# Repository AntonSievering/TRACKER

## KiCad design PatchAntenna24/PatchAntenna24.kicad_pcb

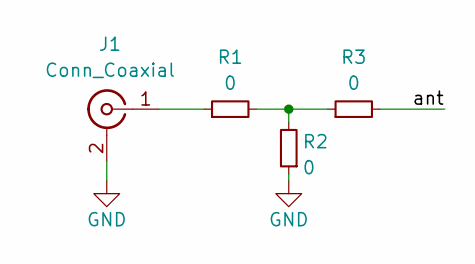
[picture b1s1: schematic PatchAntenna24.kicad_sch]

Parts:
J1: Conn_Coaxial; SMA_Amphenol_132289_EdgeMount
R1, R2, R3: 0; R_0402_1005Metric

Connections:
/ant: R3.2
GND: J1.2 (Ext), R2.1
unnamed: J1.1 (In), R1.1
unnamed: R1.2, R2.2, R3.1

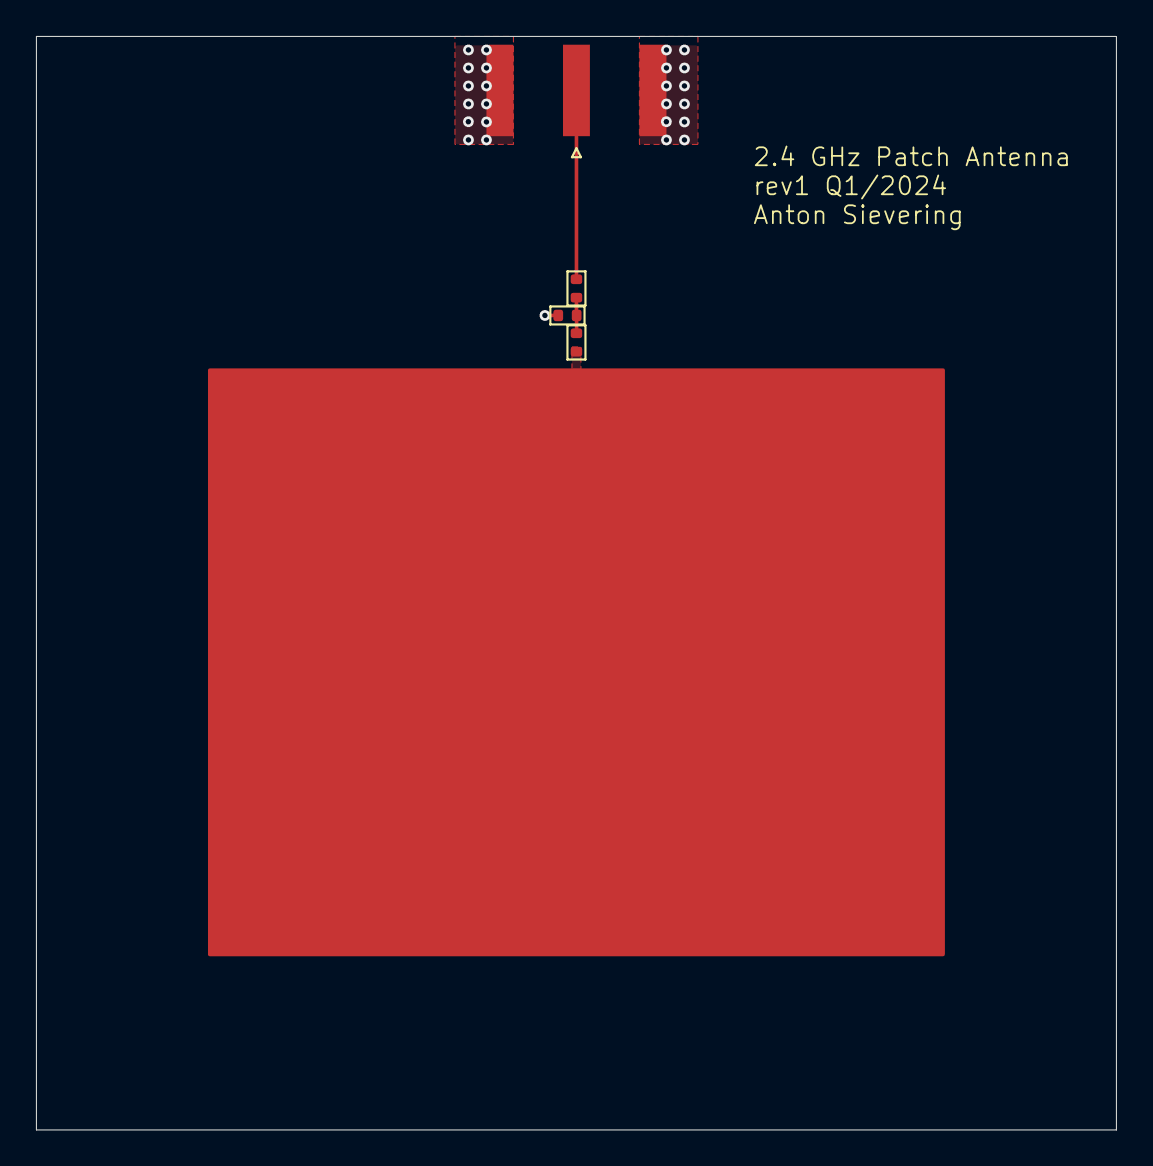
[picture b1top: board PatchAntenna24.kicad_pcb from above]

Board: 4 copper layers, 60.0 x 60.8 mm, 4 parts (0 on the bottom side), 3 nets.

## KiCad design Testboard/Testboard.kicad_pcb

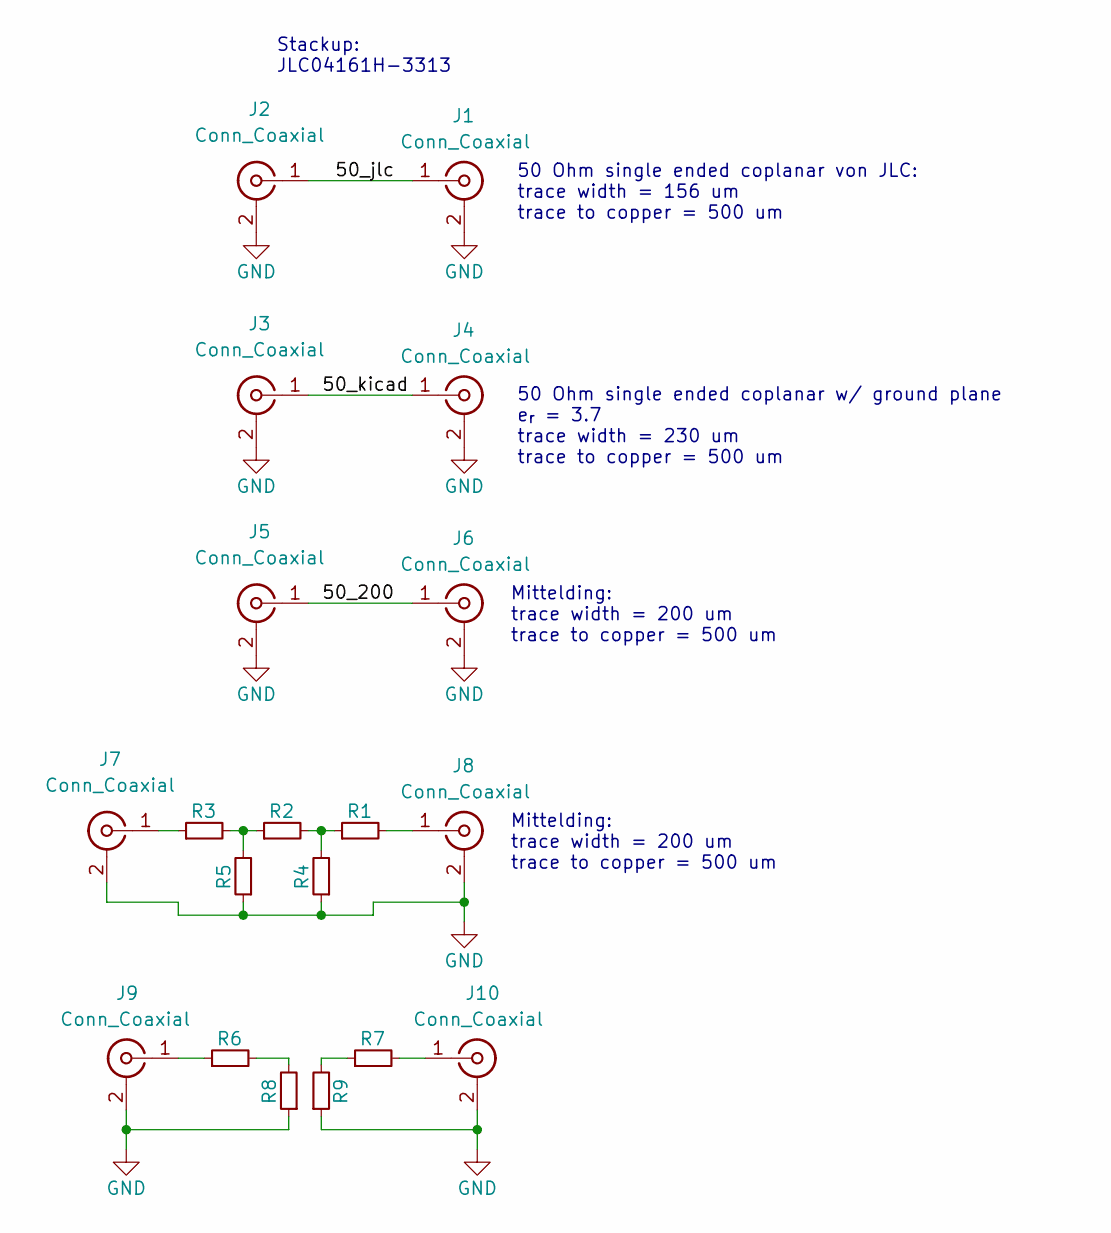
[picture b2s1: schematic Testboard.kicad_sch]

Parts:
J1, J2, J3, J4, J5, J6, J7, J8, J9, J10: Conn_Coaxial; SMA_Amphenol_132289_EdgeMount
R1, R2, R3, R4, R5, R6, R7, R8, R9: R_Small; R_0603_1608Metric

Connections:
/50_200: J5.1 (In), J6.1 (In)
/50_jlc: J1.1 (In), J2.1 (In)
/50_kicad: J3.1 (In), J4.1 (In)
GND: J1.2 (Ext), J2.2 (Ext), J3.2 (Ext), J4.2 (Ext), J5.2 (Ext), J6.2 (Ext), J7.2 (Ext), J8.2 (Ext), J9.2 (Ext), J10.2 (Ext), R4.1, R5.1, R8.1, R9.1
unnamed: J7.1 (In), R3.1
unnamed: J8.1 (In), R1.2
unnamed: J9.1 (In), R6.1
unnamed: J10.1 (In), R7.2
unnamed: R1.1, R2.2, R4.2
unnamed: R2.1, R3.2, R5.2
unnamed: R6.2, R8.2
unnamed: R7.1, R9.2

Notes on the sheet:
50 Ohm single ended coplanar von JLC: trace width = 156 um trace to copper = 500 um
Stackup: JLC04161H-3313
50 Ohm single ended coplanar w/ ground plane e_{r} = 3.7 trace width = 230 um trace to copper = 500 um
Mittelding: trace width = 200 um trace to copper = 500 um

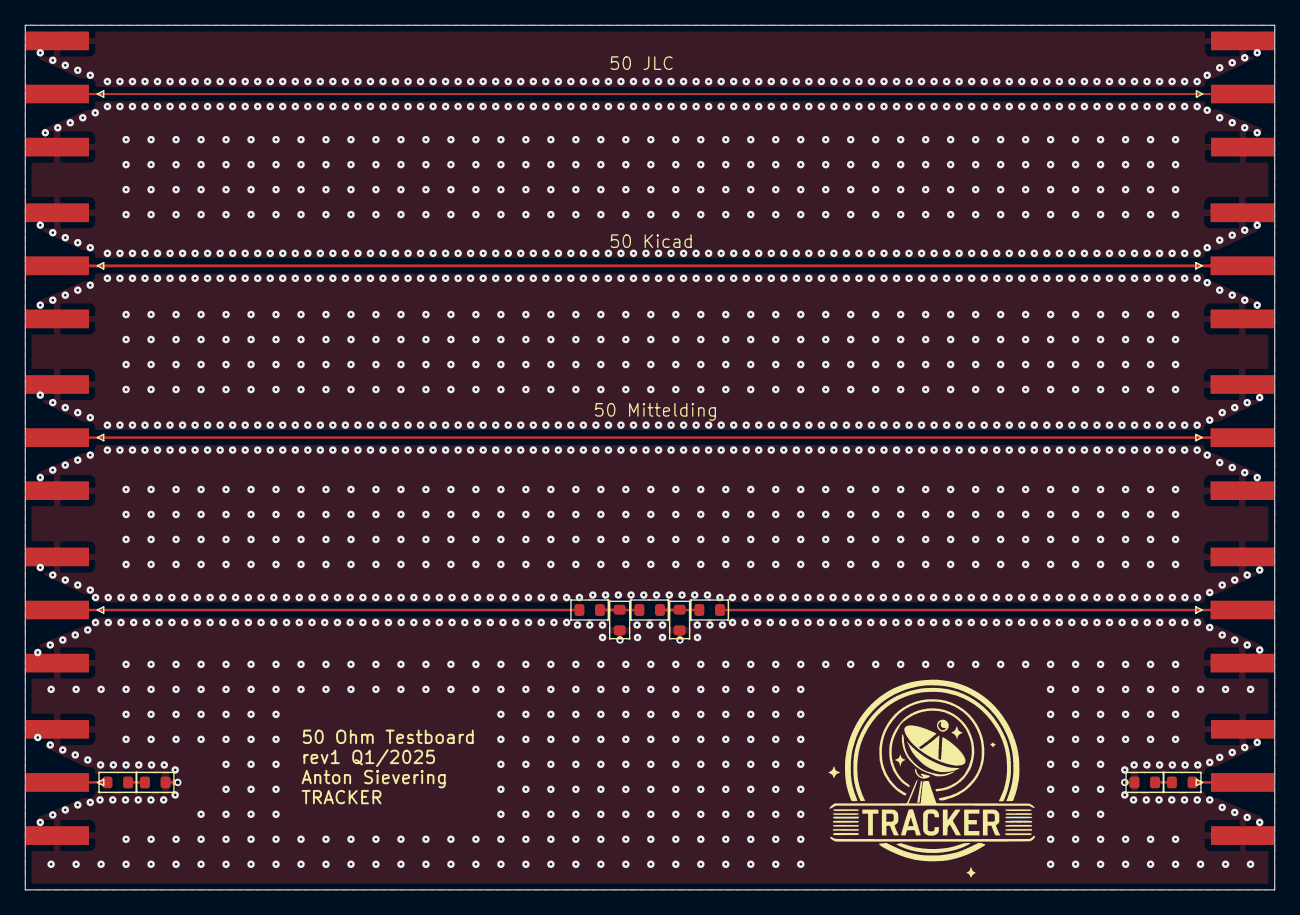
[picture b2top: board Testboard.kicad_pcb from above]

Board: 4 copper layers, 100.0 x 69.2 mm, 19 parts (0 on the bottom side), 12 nets.

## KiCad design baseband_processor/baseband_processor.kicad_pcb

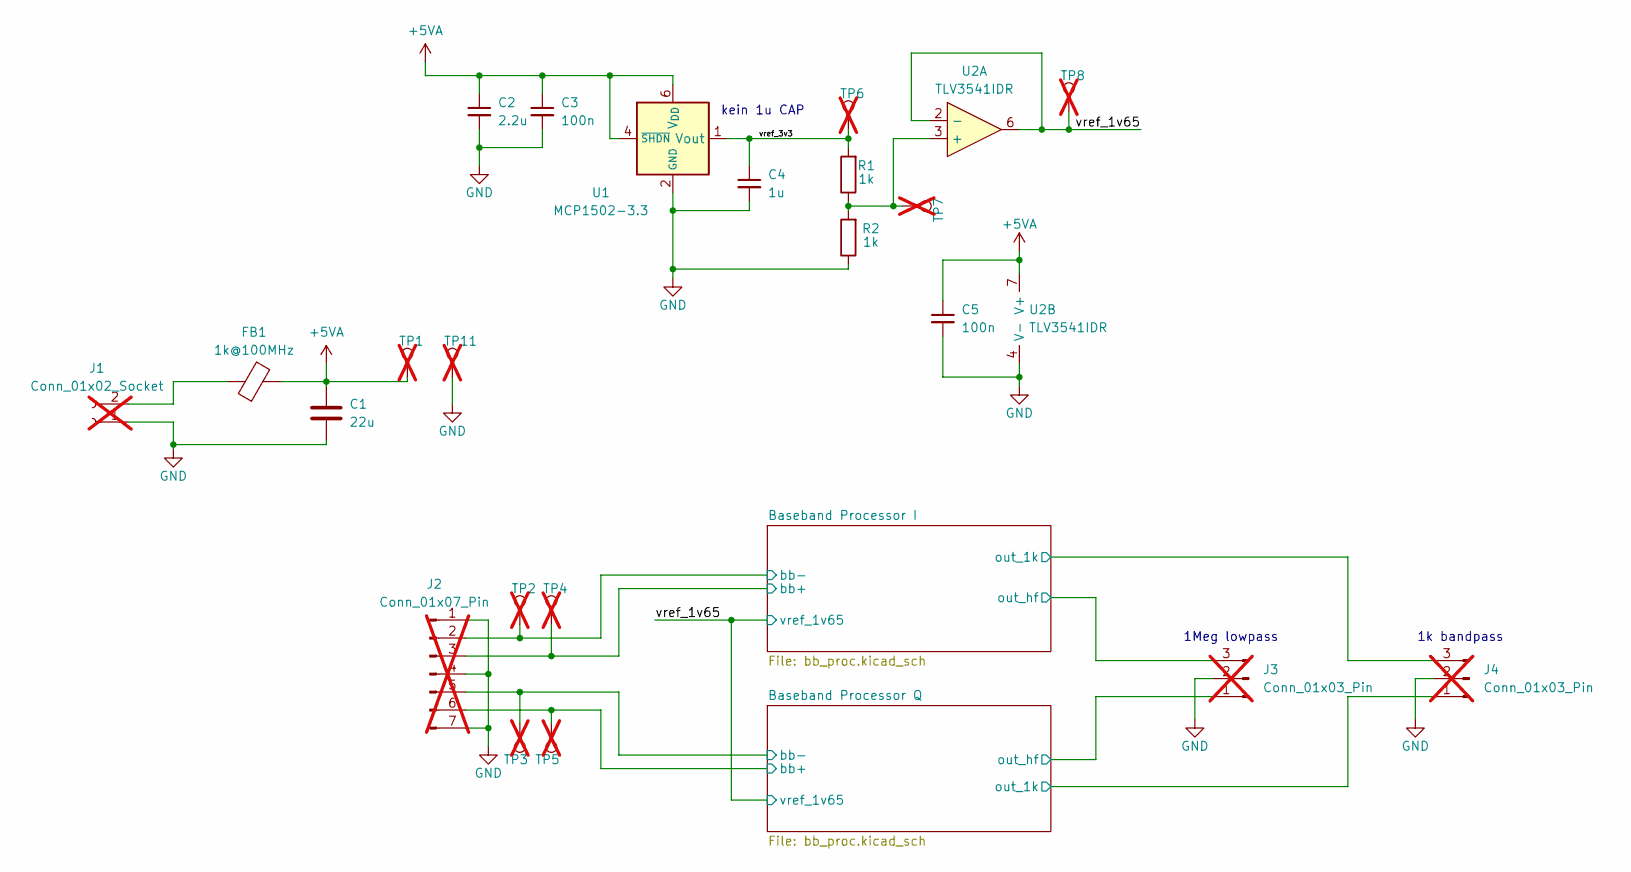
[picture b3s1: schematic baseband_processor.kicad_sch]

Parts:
C1: 22u; R_0805_2012Metric
C2: 2.2u; C_0603_1608Metric
C3, C5: 100n; C_0603_1608Metric
C4: 1u; C_0603_1608Metric
FB1: 1k@100MHz; L_0603_1608Metric; MPN 81-BLM18KG102SH1D
J1: Conn_01x02_Socket; PinHeader_1x02_P2.54mm_Vertical; not fitted
J2: Conn_01x07_Pin; PinHeader_1x07_P2.54mm_Vertical; not fitted
J3, J4: Conn_01x03_Pin; PinHeader_1x03_P2.54mm_Vertical; not fitted
R1, R2: 1k; R_0603_1608Metric
TP1, TP2, TP3, TP4, TP5, TP6, TP7, TP8, TP11: TestPoint; TestPoint_Pad_D1.0mm; not fitted
U1: MCP1502-3.3; TSOT-23-6; MPN 579-MCP1502T-33E/CHY
U2: TLV3541IDR; SOIC-8_3.9x4.9mm_P1.27mm; MPN TLV3541IDR

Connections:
+5VA: C1.1, C2.1, C3.1, C5.1, FB1.2, TP1.1, U1.4 (~SHDN), U1.6 (V_{DD}), U2.7 (V+); also elsewhere on the board
/Baseband Processor I/bb+: J2.3, TP4.1; also elsewhere on the board
/Baseband Processor I/bb-: J2.2, TP2.1; also elsewhere on the board
/Baseband Processor I/out_1k: J4.3; also elsewhere on the board
/Baseband Processor I/out_hf: J3.3; also elsewhere on the board
/Baseband Processor Q/bb+: J2.6, TP5.1; also elsewhere on the board
/Baseband Processor Q/bb-: J2.5, TP3.1; also elsewhere on the board
/Baseband Processor Q/out_1k: J4.1; also elsewhere on the board
/Baseband Processor Q/out_hf: J3.1; also elsewhere on the board
/vref_1v65: TP8.1, U2.2 (-), U2.6; also elsewhere on the board
/vref_3v3: C4.1, R1.2, TP6.1, U1.1 (Vout)
GND: C1.2, C2.2, C3.2, C4.2, C5.2, J1.1, J2.1, J2.4, J2.7, J3.2, J4.2, R2.1, TP11.1, U1.2 (GND), U1.3 (GND), U1.5 (GND), U2.4 (V-); also elsewhere on the board
unnamed: FB1.1, J1.2
unnamed: R1.1, R2.2, TP7.1, U2.3 (+)

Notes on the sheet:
1k bandpass
1Meg lowpass
kein 1u CAP

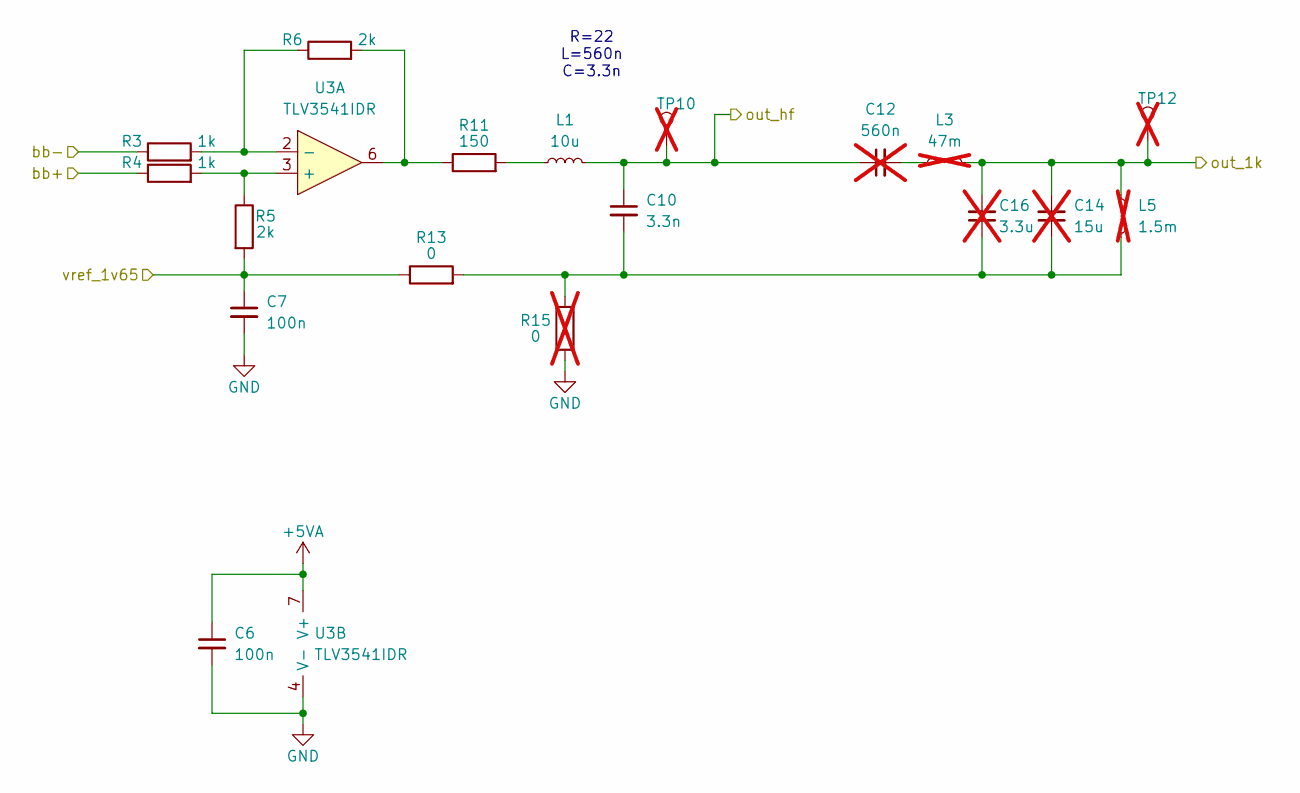
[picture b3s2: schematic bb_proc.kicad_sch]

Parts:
C6, C7: 100n; C_0603_1608Metric
C10: 3.3n; R_0603_1608Metric; MPN GCD188R71H332KA1D
C12: 560n; C_0603_1608Metric; MPN CC603KRX7R7BB564; not fitted
C14: 15u; C_0805_2012Metric; MPN C2012X6S1C156M2A; not fitted
C16: 3.3u; C_0805_2012Metric; MPN 0805X335K250CT; not fitted
L1: 10u; R_0603_1608Metric; MPN MLZ2012M100HT000
L3: 47m; L_Radial_D7.0mm_P3.00mm; MPN RLB0812-473KL; not fitted
L5: 1.5m; L_Radial_D7.0mm_P3.00mm; MPN RLB0608-152KL; not fitted
R3, R4: 1k; R_0603_1608Metric
R5, R6: 2k; R_0603_1608Metric
R11: 150; R_0603_1608Metric
R13: 0; R_0603_1608Metric
R15: 0; R_0603_1608Metric; not fitted
TP10, TP12: TestPoint; TestPoint_Pad_D1.0mm; not fitted
U3: TLV3541IDR; SOIC-8_3.9x4.9mm_P1.27mm; MPN TLV3541IDR

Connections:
+5VA: C6.1, U3.7 (V+); also elsewhere on the board
/Baseband Processor I/bb+: R4.1; also elsewhere on the board
/Baseband Processor I/bb-: R3.1; also elsewhere on the board
/Baseband Processor I/out_1k: C14.2, C16.2, L3.2, L5.1, TP12.1; also elsewhere on the board
/Baseband Processor I/out_hf: C10.1, C12.1, L1.2, TP10.1; also elsewhere on the board
/vref_1v65: C7.1, R5.2, R13.1; also elsewhere on the board
GND: C6.2, C7.2, R15.1, U3.4 (V-); also elsewhere on the board
unnamed: C10.2, C14.1, C16.1, L5.2, R13.2, R15.2
unnamed: C12.2, L3.1
unnamed: L1.1, R11.2
unnamed: R6.2, R11.1, U3.6
unnamed: R4.2, R5.1, U3.3 (+)
unnamed: R3.2, R6.1, U3.2 (-)

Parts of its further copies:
C8, C9: 100n; C_0603_1608Metric
C11: 3.3n; R_0603_1608Metric; MPN GCD188R71H332KA1D
C13: 560n; C_0603_1608Metric; MPN CC603KRX7R7BB564; not fitted
C15: 15u; C_0805_2012Metric; MPN C2012X6S1C156M2A; not fitted
C17: 3.3u; C_0805_2012Metric; MPN 0805X335K250CT; not fitted
L2: 10u; R_0603_1608Metric; MPN MLZ2012M100HT000
L4: 47m; L_Radial_D7.0mm_P3.00mm; MPN RLB0812-473KL; not fitted
L6: 1.5m; L_Radial_D7.0mm_P3.00mm; MPN RLB0608-152KL; not fitted
R7, R8: 1k; R_0603_1608Metric
R9, R10: 2k; R_0603_1608Metric
R12: 150; R_0603_1608Metric
R14: 0; R_0603_1608Metric
R16: 0; R_0603_1608Metric; not fitted
TP9, TP13: TestPoint; TestPoint_Pad_D1.0mm; not fitted
U4: TLV3541IDR; SOIC-8_3.9x4.9mm_P1.27mm; MPN TLV3541IDR

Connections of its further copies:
+5VA: C8.1, U4.7 (V+); also elsewhere on the board
/Baseband Processor Q/bb+: R8.1; also elsewhere on the board
/Baseband Processor Q/bb-: R7.1; also elsewhere on the board
/Baseband Processor Q/out_1k: C15.2, C17.2, L4.2, L6.1, TP13.1; also elsewhere on the board
/Baseband Processor Q/out_hf: C11.1, C13.1, L2.2, TP9.1; also elsewhere on the board
/vref_1v65: C9.1, R9.2, R14.1; also elsewhere on the board
GND: C8.2, C9.2, R16.1, U4.4 (V-); also elsewhere on the board
unnamed: C11.2, C15.1, C17.1, L6.2, R14.2, R16.2
unnamed: C13.2, L4.1
unnamed: L2.1, R12.2
unnamed: R10.2, R12.1, U4.6
unnamed: R8.2, R9.1, U4.3 (+)
unnamed: R7.2, R10.1, U4.2 (-)

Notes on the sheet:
R=22 L=560n C=3.3n

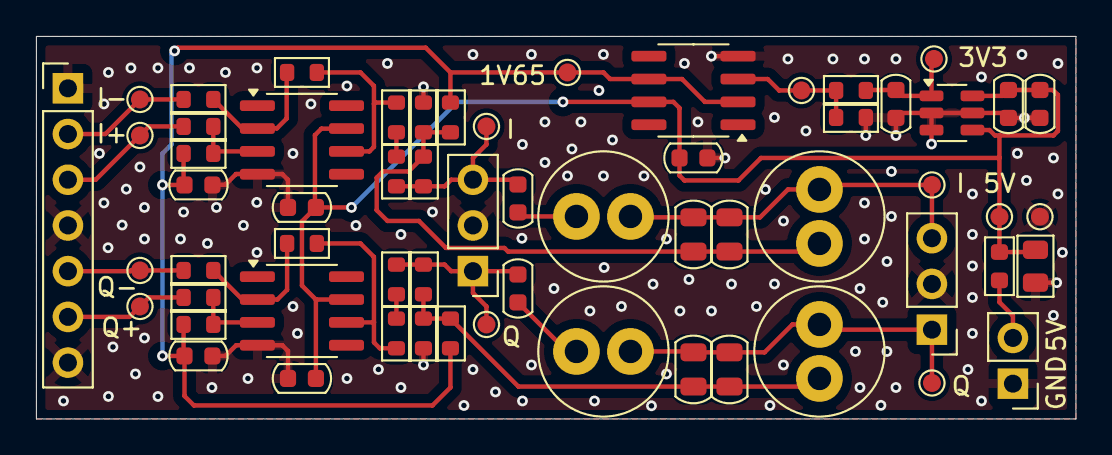
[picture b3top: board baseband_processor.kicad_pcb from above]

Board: 2 copper layers, 57.8 x 21.2 mm, 61 parts (0 on the bottom side), 26 nets.

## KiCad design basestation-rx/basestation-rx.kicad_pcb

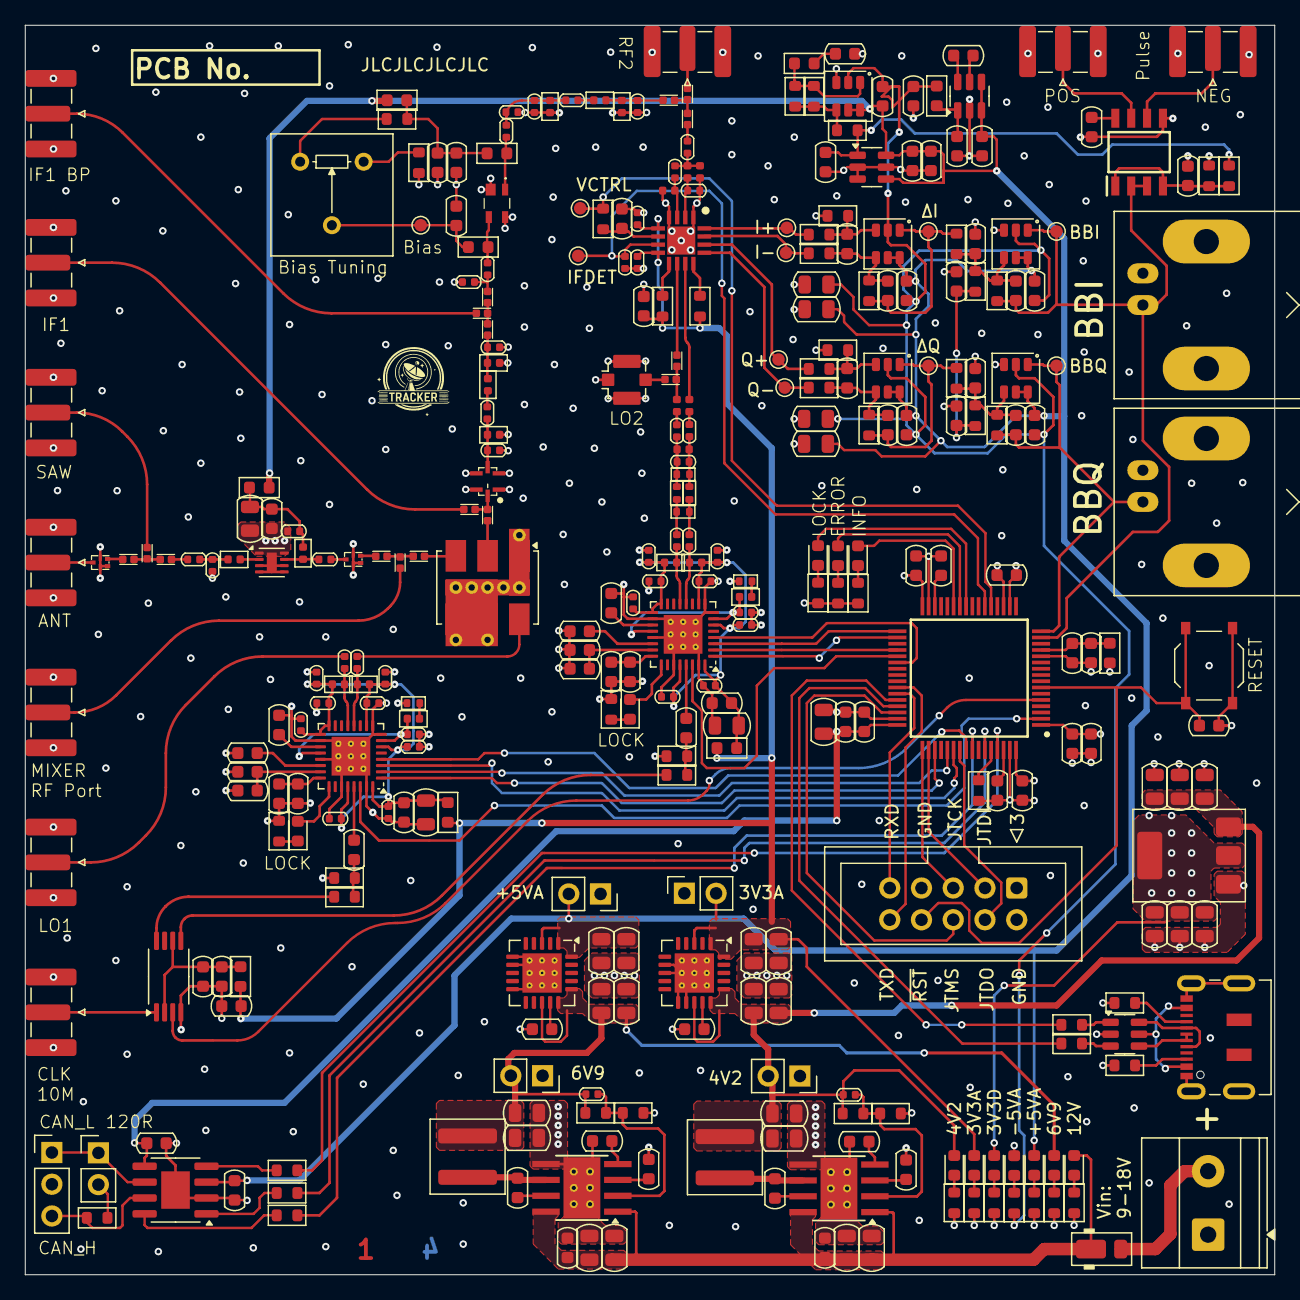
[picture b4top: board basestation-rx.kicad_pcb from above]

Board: 4 copper layers, 100.0 x 100.0 mm, 332 parts (0 on the bottom side), 185 nets.

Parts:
C1, C6, C7, C8, C9, C10, C11, C14, C15, C17, C21, C36, C40, C62, C70, C75, C84, C85, C93, C94, C102, C104, C106, C113, C114, C122, C123, C146, C147: 100n; C_0603_1608Metric
C1_LF1, C1_LF2, C33, C34, C52, C53, C79, C80: 1n; C_0402_1005Metric
C2, C3, C25, C44, C103, C107, C112, C120, C121: 2.2u; C_0603_1608Metric
C2_LF1, C2_LF2: 6.8n; L_0402_1005Metric
C4, C16, C35, C60, C87, C88, C96, C97, C100, C108, C109, C110, C111, C130, C131, C132, C133, C134, C135: 10u; C_0805_2012Metric
C5, C12, C13, C78, C86, C95, C101, C105, C115, C116, C117, C137, C138, C145: 1u; C_0603_1608Metric
C18, C19, C20, C22, C23, C24, C31, C32, C37, C38, C39, C41, C42, C43, C50, C51, C64, C69, C72, C124, C125: 100p; C_0402_1005Metric
C26, C29, C45, C48: 22u; C_0603_1608Metric
C27, C28, C30, C46, C47, C49: 10u; C_0603_1608Metric
C54: 91p; C_0402_1005Metric
C55, C56, C81: 1.5p; C_0402_1005Metric
C57, C66: 27p; C_0402_1005Metric
C58, C67: 3.3p; C_0402_1005Metric
C59, C68: 180p; C_0402_1005Metric
C61: 12p; C_0402_1005Metric
C63: Tuning; C_0402_1005Metric
C65: 2.7p; C_0402_1005Metric
C71, C73, C82, C83, C89, C90, C91, C92, C98, C99: 1n; C_0603_1608Metric
C74: 56p; C_0402_1005Metric
C76, C77: 5.6p; C_0402_1005Metric
C118, C119: 3.3n; C_0603_1608Metric
C126, C127, C128, C129: 22u; C_0805_2012Metric
C136, C139, C140, C141, C142, C143, C144: 47u; C_0805_2012Metric
C148, C149: 15p; C_0402_1005Metric
D1, D2, D3, D4, D5, D6, D7, D8, D9, D11, D12, D13: LED; D_0603_1608Metric
D10: DFLS130; D_PowerDI-123
FB1, FB2, FB3, FB4, FB5, FB6, FB7, FB8: 1k@100MHz; L_0603_1608Metric
IC1: STM32H562RGT6; QFP50P1200X1200X160-64N
IC2, IC3: LMX2581SQE_NOPB; QFN-32-1EP_5x5mm_P0.5mm_EP3.1x3.1mm_ThermalVias
IC4: SAV-551+; SAV551
IC5: LT5546EUF#PBF; QFN65P400X400X80-17N-D
IC6: LMK1C1104PWR; TSSOP-8_4.4x3mm_P0.65mm
J1, J2, J3, J4, J5, J6, J8, J9, J20, J21: SMA; SMA_Edge_Mount
J7: U.FL; U.FL_Molex_MCRF_73412-0110_Vertical
J10: USB_C_Receptacle_USB2.0_16P; USB_C_Receptacle_JAE_DX07S016JA1R1500
J11: Conn_01x02_Pin; PinHeader_1x02_P2.54mm_Vertical
J12: Conn_01x03_Pin; PinHeader_1x03_P2.54mm_Vertical
J13, J15, J16, J17: Conn_01x02_Pin; PinSocket_1x02_P2.54mm_Vertical
J14: Conn_02x05_Counter_Clockwise; IDC-Header_2x05_P2.54mm_Vertical
J18: Screw_Terminal_01x02; TerminalBlock_Phoenix_MKDS-1,5-2-5.08_1x02_P5.08mm_Horizont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
J19, J22: BNC; BNC_Amphenol_B6252HB-NPP3G-50_Horizontal
L1, L2, L3, L4: 18n; L_0402_1005Metric
L5: 1.8n; L_0402_1005Metric
L6, L7: 110n; L_0402_1005Metric
L8, L13: 24n; L_0402_1005Metric
L9, L14: 200n; L_0402_1005Metric
L10, L12, L15: 3.6n; L_0402_1005Metric
L11: 1.5n; L_0402_1005Metric
L16, L17: 560n; L_0603_1608Metric
L18: 120n; L_0402_1005Metric
L19, L20: 56n; L_0402_1005Metric
L23, L24: 3.3u; L_Coilcraft_XAL5030
R1, R4, R41: 1k; R_0603_1608Metric
R2, R3, R6, R7, R8, R9, R10, R11, R13, R14, R15, R16, R17, R18, R19, R20: 0; RF_JUMPER
R2_LF1, R2_LF2: 820R; R_0402_1005Metric
R5, R21, R22, R23, R24, R28, R42, R43: 0; R_0603_1608Metric
R25: 120; R_0603_1608Metric
R26, R27: 5.6k; R_0603_1608Metric
R29, R32, R35, R59, R60, R61, R62, R63, R64, R65, R66, R67, R68, R74, R75: 10k; R_0603_1608Metric
R30, R31, R33, R34: 25R; R_0603_1608Metric
R36, R39: 330R; R_0402_1005Metric
R37, R38: 33R; R_0402_1005Metric
R40, R46, R47, R53, R54: 2k 0.1%; R_0603_1608Metric
R44, R45, R48, R49, R50, R51, R52, R55, R56, R57: 1k 0.1%; R_0603_1608Metric
R69: 180k; R_0603_1608Metric
R70, R72: 22k; R_0603_1608Metric
R71, R73: 100k; R_0603_1608Metric
RV1: 10k; Potentiometer_Bourns_3386F_Vertical
SW1: SW_Push; SW_Push_1P1T_XKB_TS-1187A
TP1, TP2, TP3, TP4, TP5, TP6, TP7, TP8, TP9, TP10, TP11: TestPoint; TestPoint_Pad_D1.0mm
U1, U2: AFS14A72-2436.00-T3; AFS14A72
U3: ADE-3G+; Mini-Circuits_CD542_LandPatternPL-052
U4: USBLC6-2SC6; SOT-23-6
U5: MCP2542FDxMF; SOIC-8-1EP_3.9x4.9mm_P1.27mm_EP2.29x3mm
U6: GRF2081; DFN-8-1EP_2x2mm_P0.5mm_EP0.8x1.6mm
U7, U8, U9, U10, U12: LMH6611MK; SOT-23-6
U11: MCP1502-3.3; TSOT-23-6
U13: LM2776; SOT-23-6
U14, U15: BD9D321EFJ; Texas_HTSOP-8-1EP_3.9x4.9mm_P1.27mm_EP2.95x4.9mm_Mask2.4x3.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
U16: LT1117CST-3.3; SOT-223-3_TabPin2
U17, U18: TPS7A4701xRGW; Texas_RGW0020A_VQFN-20-1EP_5x5mm_P0.65mm_EP3.15x3.15mm_Ther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
U19: TLV3501; SOIC127P600X175-8N
U20: 748111009

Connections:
+3.3V: C4.1, C5.1, C6.1, C7.1, C8.1, C9.1, C10.1, C12.1, C14.1, C136.1, C141.1, C144.1, D8.2 (A), FB1.2, IC1.1 (VBAT), IC1.19 (VDD_1), IC1.32 (VDD_2), IC1.48 (VDD_3), IC1.64 (VDD_4), J14.1, U5.5 (VIO), U16.2 (OUT)
+3.3VA: C78.2, C79.2, C80.2, C140.1, C143.1, C145.1, D7.2 (A), FB2.2, FB3.2, FB6.2, IC5.5 (VCC), IC5.8 (VCC_1), J15.2, R42.2, R43.2, U18.1 (OUT), U18.3 (SENSE/FB), U18.20 (OUT)
+3V3: C147.1, U19.8 (V_{cc})
+5VA: C15.1, C84.1, C85.1, C88.1, C93.1, C94.1, C97.1, C103.1, C104.1, C106.1, C112.1, C139.1, C142.1, D6.2 (A), FB4.1, FB5.1, J13.2, U5.3 (VDD), U7.5 (~CS), U7.6 (V+), U8.5 (~CS), U8.6 (V+), U9.5 (~CS), U9.6 (V+), U10.5 (~CS), U10.6 (V+), U11.4 (~SHDN), U11.6 (V_{DD}), U12.5 (~CS), U12.6 (V+), U13.3 (VIN), U13.4 (EN), U17.1 (OUT), U17.3 (SENSE/FB), U17.20 (OUT)
-5VA: C84.2, C85.2, C87.1, C93.2, C94.2, C96.1, C106.2, C121.1, FB8.2, R68.2, U7.2 (V-), U8.2 (V-), U9.2 (V-), U10.2 (V-), U12.2 (V-)
/400MHz BP/RF_{in+}: C52.2, R36.2, R37.1
/400MHz BP/RF_{in-}: C53.2, R36.1, R38.2
/400MHz BP/RF_{out+}: IC5.11 (2XLO+), L6.2
/400MHz BP/RF_{out-}: L7.2, R13.1, R14.2
/Channel pre-filter 1/RF_{in}: C66.1, C67.1, L13.1, U20.4 (OUT)
/Channel pre-filter 1/RF_{out}: C68.1, L14.2, L15.1, R15.1
/Channel pre-filter 2/RF_{in}: C57.1, C58.1, C72.2, C149.2, L8.1
/Channel pre-filter 2/RF_{out}: C59.1, L9.2, L10.1, R18.1
/FDCAN/CAN_H: J12.3, R25.2, U5.7 (CANH)
/FDCAN/CAN_L: J11.1, J12.1, U5.6 (CANL)
/FDCAN/CAN_RX: R23.2, U5.4 (RXD)
/FDCAN/CAN_TX: R5.2, U5.1 (TXD)
/FDCAN/STBY: R24.2, U5.8 (STBY)
/LED1: D11.2 (A), IC1.26 (PB0)
/LED2: D12.2 (A), IC1.27 (PB1)
/LED3: D13.2 (A), IC1.25 (PC5)
/LNA 2.45G/RF_{in}: C61.1, R6.2
/LNA 2.45G/RF_{out}: C65.2, U2.C (in)
/LNA 200M/RF_{in}: C69.1, C148.2, R17.2
/LNA 200M/lna_bias: C73.1, L16.1, RV1.2, TP9.1
/LNA 200M/lna_rfin: C69.2, IC4.3, L16.2
/LNA 200M/lna_rfout: C72.1, IC4.1, L17.2
/LNA 200M/lna_vcc: C70.1, C71.1, FB5.2, L17.1, R73.1
/Microcontroller/DEBUG_RX: IC1.43 (PA10), J14.9
/Microcontroller/DEBUG_TX: IC1.42 (PA9), J14.10
/Microcontroller/JTCK: IC1.49 (PA14), J14.5
/Microcontroller/JTDI: IC1.50 (PA15), J14.3
/Microcontroller/JTDO: IC1.55 (PB3), J14.4
/Microcontroller/JTMS: IC1.46 (PA13), J14.6
/Microcontroller/NRST: C1.1, IC1.7 (NRST), J14.8, SW1.1
/Microcontroller/PA1: C99.2, IC1.15 (PA1), J19.1 (In), R57.2, TP8.1, U10.1, U19.2 (-), U19.3 (+)
/Microcontroller/PA2: C90.2, IC1.16 (PA2), J22.1 (In), R50.2, TP4.1, U8.1
/Microcontroller/PA5: IC1.21 (PA5), R41.2, TP11.1
/Microcontroller/PA6: C81.2, IC1.22 (PA6), IC5.7 (IFDET), TP10.1
/Microcontroller/PA11: IC1.44 (PA11), R22.1
/Microcontroller/PA12: IC1.45 (PA12), R21.1
/Microcontroller/PB5: IC1.57 (PB5), R24.1
/Microcontroller/PB7: IC1.59 (PB7), R5.1
/Microcontroller/PB8: IC1.61 (PB8), R23.1
/Microcontroller/boot0_r: IC1.60 (BOOT0), R28.2
/Microcontroller/cpu_clock: IC1.5 (PH0-OSC_IN), IC6.3 (Y0)
/Microcontroller/stm32_vdda: C11.1, C13.1, FB1.1, IC1.13 (VDDA)
/Microcontroller/stm_vcap1: C2.1, IC1.30 (VCAP_1)
/Microcontroller/stm_vcap2: C3.1, IC1.62 (VCAP_2)
/NEG_EDGE: J20.1 (In), U19.7
/PLL1/RF_{out}+: C33.2, U3.6 (LO)
/PLL1/RF_{out}-: C34.2, J4.1 (In)
/PLL1/f_{refin}: IC6.8 (Y1), R30.1
/PLL1/pll_3v3: C16.1, C17.1, C18.1, C19.1, C20.1, C22.1, C23.1, C24.1, C31.1, C32.1, FB2.1, IC2.6 (VCCCP), IC2.10 (VCCPLL), IC2.16 (VCCBUF), IC2.17 (VCCVCO), IC2.28 (VCCDIG), IC2.32 (VCCFRAC), L1.1, L2.1
/PLL1_CE: IC1.56 (PB4), IC2.4 (CE)
/PLL1_CLK: IC1.51 (PC10), IC2.1 (CLK)
/PLL1_DATA: IC1.53 (PC12), IC2.2 (DATA)
/PLL1_LE: IC1.54 (PD2), IC2.3 (LE)
/PLL1_MUXOUT: IC1.2 (PC13), IC2.30 (MUXOUT)
/PLL2/f_{refin}: IC6.5 (Y2), R33.1
/PLL2/pll_3v3: C35.1, C36.1, C37.1, C38.1, C39.1, C41.1, C42.1, C43.1, C50.1, C51.1, FB3.1, IC3.6 (VCCCP), IC3.10 (VCCPLL), IC3.16 (VCCBUF), IC3.17 (VCCVCO), IC3.28 (VCCDIG), IC3.32 (VCCFRAC), L3.1, L4.1
/PLL2_CE: IC1.38 (PC7), IC3.4 (CE)
/PLL2_CLK: IC1.34 (PB13), IC3.1 (CLK)
/PLL2_DATA: IC1.36 (PB15), IC3.2 (DATA)
/PLL2_LE: IC1.33 (PB12), IC3.3 (LE)
/PLL2_MUXOUT: IC1.37 (PC6), IC3.30 (MUXOUT)
/POS_EDGE: J21.1 (In), U19.6
/Power Supply/dcdc_4v2: C100.1, C125.1, C127.1, C129.1, C131.1, C132.1, C134.1, C135.1, D5.2 (A), J17.2, L24.2, R71.1, U16.3 (IN), U18.13 (EN), U18.15 (IN), U18.16 (IN)
/Power Supply/dcdc_6v9: C124.1, C126.1, C128.1, C130.1, C133.1, D4.2 (A), J16.2, L23.2, R69.1, U17.13 (EN), U17.15 (IN), U17.16 (IN)
/Power Supply/v_supply: C108.1, C109.1, C110.1, C111.1, C113.1, C114.1, D3.2 (A), D10.1 (K), U14.1 (EN), U14.8 (VIN), U15.1 (EN), U15.8 (VIN)
/Pulse Output Comparator/vref_1v65: C146.1, R1.2, R4.1, U19.1 (+), U19.4 (-)
/Quadrature Downconverter/2xLO-: IC5.10 (2XLO-), R14.1
/Quadrature Downconverter/Baseband Amplifier I/IQ+: IC5.16 (IOUT+), R52.1, TP6.1
/Quadrature Downconverter/Baseband Amplifier I/IQ-: IC5.15 (IOUT-), R51.1, TP5.1
/Quadrature Downconverter/Baseband Amplifier Q/IQ+: IC5.14 (QOUT+), R45.1, TP2.1
/Quadrature Downconverter/Baseband Amplifier Q/IQ-: IC5.13 (QOUT-), R44.1, TP1.1
/Quadrature Downconverter/IF_{in}: C74.1, R20.2
/Quadrature Downconverter/demod_if+: C77.2, IC5.2 (IF+), L19.2
/Quadrature Downconverter/demod_if-: C76.2, IC5.3 (IF-), L20.1
/Quadrature Downconverter/vref_n1v65: C86.1, C95.1, R48.1, R55.1
/Reference Buffer/REFIN: IC6.1 (CLKIN), J2.1 (In)
/Reference Buffer/clk_buf_vcc: C101.1, C102.1, FB6.1, IC6.2 (1G), IC6.6 (VDD)
/USB/usb_cc: J10.A5 (CC1), R27.1
/USB/usb_vbus: J10.A4 (VBUS), J10.A9 (VBUS), J10.B4 (VBUS), J10.B9 (VBUS), U4.5 (VBUS)
/USB/usb_vconn: J10.B5 (CC2), R26.1
/USB/usbd+: R21.2, U4.3 (I/O2)
/USB/usbd-: R22.2, U4.1 (I/O1)
/USB/usbdm_in: J10.A7 (D-), J10.B7 (D-), U4.6 (I/O1)
/USB/usbdp_in: J10.A6 (D+), J10.B6 (D+), U4.4 (I/O2)
/Voltage Reference -1V65/vref_3v3: C105.1, R1.1, R59.1, U11.1 (Vout)
/Voltage Reference -1V65/vref_n1v65: C107.1, FB7.2
GND: C1.2, C1_LF1.2, C1_LF2.2, C2.2, C3.2, C4.2, C5.2, C6.2, C7.2, C8.2, C9.2, C10.2, C11.2, C12.2, C13.2, C14.2, C15.2, C16.2, C17.2, C18.2, C19.2, C20.2, C22.2, C23.2, C24.2, C25.2, C26.2, C27.2, C28.2, C29.2, C30.2, C31.2, C32.2, C35.2, C36.2, C37.2, C38.2, C39.2, C41.2, C42.2, C43.2, C44.2, C45.2, C46.2, C47.2, C48.2, C49.2, C50.2, C51.2, C57.2, C59.2, C60.1, C62.1, C63.1, C64.1, C66.2, C68.2, C70.2, C71.2, C73.2, C75.1, C77.1, C78.1, C79.1, C80.1, C81.1, C86.2, C87.2, C88.2, C89.2, C95.2, C96.2, C97.2, C98.2, C100.2, C101.2, C102.2, C103.2, C104.2, C105.2, C107.2, C108.2, C109.2, C110.2, C111.2, C112.2, C113.2, C114.2, C116.2, C117.2, C118.2, C119.2, C120.2, C121.2, C126.2, C127.2, C128.2, C129.2, C130.2, C131.2, C132.2, C133.2, C134.2, C135.2, C136.2, C137.2, C138.2, C139.2, C140.2, C141.2, C142.2, C143.2, C144.2, C145.2, C146.2, C147.2, C148.1, C149.1, D9.2 (A), IC1.12 (VSSA), IC1.18 (VSS_1), IC1.31 (VSS_2), IC1.47 (VSS_3), IC1.63 (VSS_4), IC2.8 (GND_1), IC2.9 (GND_2), IC2.18 (GND_3), IC2.21 (GND_4), IC2.27 (GND_5), IC2.31 (GND_6), IC2.33 (EP), IC3.8 (GND_1), IC3.9 (GND_2), IC3.18 (GND_3), IC3.21 (GND_4), IC3.27 (GND_5), IC3.31 (GND_6), IC3.33 (EP), IC4.2, IC4.4 (GND), IC5.1 (GND), IC5.4 (GND), IC5.17 (EP), IC6.4 (GND), J1.2 (Ext), J2.2 (Ext), J3.2 (Ext), J4.2 (Ext), J5.2 (Ext), J6.2 (Ext), J7.2 (Ext), J8.2 (Ext), J9.2 (Ext), J10.A1 (GND), J10.A12 (GND), J10.B1 (GND), J10.B12 (GND), J10.S1 (SHIELD), J12.2, J13.1, J14.2, J14.7, J15.1, J16.1, J17.1, J18.1, J19.2 (Ext), J20.2 (Ext), J21.2 (Ext), J22.2 (Ext), L8.2, L10.2, L13.2, L15.2, L18.2, L20.2, R2_LF1.2, R2_LF2.2, R4.2, R26.2, R27.2, R28.1, R29.2, R31.2, R32.2, R34.2, R35.2, R40.2, R46.2, R53.2, R62.2, R63.2, R64.2, R65.2, R66.2, R67.2, R70.2, R72.2, R74.2, R75.2, SW1.2, U1.B (GND), U1.D (GND), U1.E (GND), U2.B (GND), U2.D (GND), U2.E (GND), U3.1 (GND), U3.4 (GND), U3.5 (GND), U4.2 (GND), U5.2 (VSS), U5.9 (VSS), U6.1, U6.3 (GND), U6.4 (GND), U6.5 (GND), U6.6 (SHDN), U6.8 (GND), U6.9 (GND), U8.3 (+), U10.3 (+), U11.2 (GND), U11.3 (GND), U11.5 (GND), U12.3 (+), U13.2 (GND), U14.5 (GND), U14.9 (GND), U15.5 (GND), U15.9 (GND), U16.1, U17.6 (3.2V), U17.7 (GND), U17.10 (0.4V), U17.21 (EP), U18.7 (GND), U18.8 (1.6V), U18.11 (0.2V), U18.12 (0.1V), U18.21 (EP), U19.5 (GND), U20.1, U20.3, U20.5, U20.7
unnamed: C2_LF1.2, R2_LF1.1
unnamed: C2_LF2.2, R2_LF2.1
unnamed: C21.1, R30.2, R31.1
unnamed: C40.1, R33.2, R34.1
unnamed: C54.1, C55.1, L5.1, R37.2, R39.2
unnamed: C54.2, C56.1, L5.2, R38.1, R39.1
unnamed: C55.2, L6.1
unnamed: C56.2, L7.1
unnamed: C58.2, L9.1
unnamed: C60.2, C62.2, C64.2, FB4.2, L12.2
unnamed: C61.2, C63.2, L11.1
unnamed: C65.1, L12.1, U6.7
unnamed: C67.2, L14.1
unnamed: C74.2, C76.1, L18.1, L19.1
unnamed: C83.2, R47.2, R49.1, TP3.1, U7.1
unnamed: C92.2, R54.2, R56.1, TP7.1, U9.1
unnamed: D1.2 (A), IC2.25 (LD)
unnamed: D1.1 (K), R32.1
unnamed: D2.2 (A), IC3.25 (LD)
unnamed: D2.1 (K), R35.1
unnamed: D3.1 (K), R62.1
unnamed: D4.1 (K), R63.1
unnamed: D5.1 (K), R64.1
unnamed: D6.1 (K), R65.1
unnamed: D7.1 (K), R66.1
unnamed: D8.1 (K), R67.1
unnamed: D9.1 (K), R68.1
unnamed: D10.2 (A), J18.2
unnamed: D11.1 (K), R29.1
unnamed: D12.1 (K), R74.1
unnamed: D13.1 (K), R75.1
unnamed: FB7.1, R60.2, R61.2, U12.1
unnamed: C1_LF1.1, C2_LF1.1, IC2.7 (CPOUT), IC2.20 (VTUNE)
unnamed: C21.2, IC2.29 (OSCIN)
unnamed: C33.1, IC2.12 (RFOUTA+), L2.2
unnamed: C34.1, IC2.13 (RFOUTA-), L1.2
unnamed: C29.1, C30.1, IC2.23 (VBIASCOMP)
unnamed: C28.1, IC2.19 (VBIASVCO)
unnamed: C25.1, IC2.22 (VREFVCO)
unnamed: C26.1, C27.1, IC2.24 (VREGVCO)
unnamed: C1_LF2.1, C2_LF2.1, IC3.7 (CPOUT), IC3.20 (VTUNE)
unnamed: C40.2, IC3.29 (OSCIN)
unnamed: C52.1, IC3.12 (RFOUTA+), L4.2
unnamed: C53.1, IC3.13 (RFOUTA-), L3.2
unnamed: C48.1, C49.1, IC3.23 (VBIASCOMP)
unnamed: C47.1, IC3.19 (VBIASVCO)
unnamed: C44.1, IC3.22 (VREFVCO)
unnamed: C45.1, C46.1, IC3.24 (VREGVCO)
unnamed: IC5.9 (EN), R43.1
unnamed: IC5.12 (STBY), R42.1
unnamed: C75.2, IC5.6 (VCTRL), R41.1
unnamed: J1.1 (In), U1.C (in)
unnamed: J3.1 (In), R3.2
unnamed: J5.1 (In), R8.2
unnamed: J6.1 (In), R11.2
unnamed: J7.1 (In), R13.2
unnamed: J8.1 (In), R16.2
unnamed: J9.1 (In), R19.2
unnamed: J11.2, R25.1
unnamed: L11.2, U6.2
unnamed: R2.2, R3.1, R6.1
unnamed: R7.2, R8.1, R9.1
unnamed: R15.2, R16.1, R17.1
unnamed: R18.2, R19.1, R20.1
unnamed: R40.1, RV1.3
unnamed: R73.2, RV1.1
unnamed: R2.1, U1.A (out)
unnamed: R7.1, U2.A (out)
unnamed: R10.1, U3.2 (IF)
unnamed: R9.2, U3.3 (RF)
unnamed: C82.2, R45.2, R46.1, U7.3 (+)
unnamed: C82.1, C83.1, R44.2, R47.1, U7.4 (-)
unnamed: C89.1, C90.1, R48.2, R49.2, R50.1, U8.4 (-)
unnamed: C91.2, R52.2, R53.1, U9.3 (+)
unnamed: C91.1, C92.1, R51.2, R54.1, U9.4 (-)
unnamed: C98.1, C99.1, R55.2, R56.2, R57.1, U10.4 (-)
unnamed: R59.2, R60.1, R61.1, U12.4 (-)
unnamed: C115.1, U13.5 (C1+)
unnamed: C115.2, U13.6 (C1-)
unnamed: C120.1, FB8.1, U13.1 (VOUT)
unnamed: C122.1, U14.7 (BOOT)
unnamed: C124.2, R69.2, R70.1, U14.2 (FB)
unnamed: C118.1, U14.4 (SS)
unnamed: C122.2, L23.1, U14.6 (SW)
unnamed: C116.1, U14.3 (VREG)
unnamed: C123.1, U15.7 (BOOT)
unnamed: C125.2, R71.2, R72.1, U15.2 (FB)
unnamed: C119.1, U15.4 (SS)
unnamed: C123.2, L24.1, U15.6 (SW)
unnamed: C117.1, U15.3 (VREG)
unnamed: C137.1, U17.14 (NR)
unnamed: C138.1, U18.14 (NR)
unnamed: R10.2, R11.1, U20.8 (IN)
